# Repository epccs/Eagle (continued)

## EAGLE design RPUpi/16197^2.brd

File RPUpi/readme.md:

[RPUpi]

Shield to interface a Pi Zero hardware UART with a managed multidrop serial.

[RPUpi]: https://github.com/epccs/RPUpi/

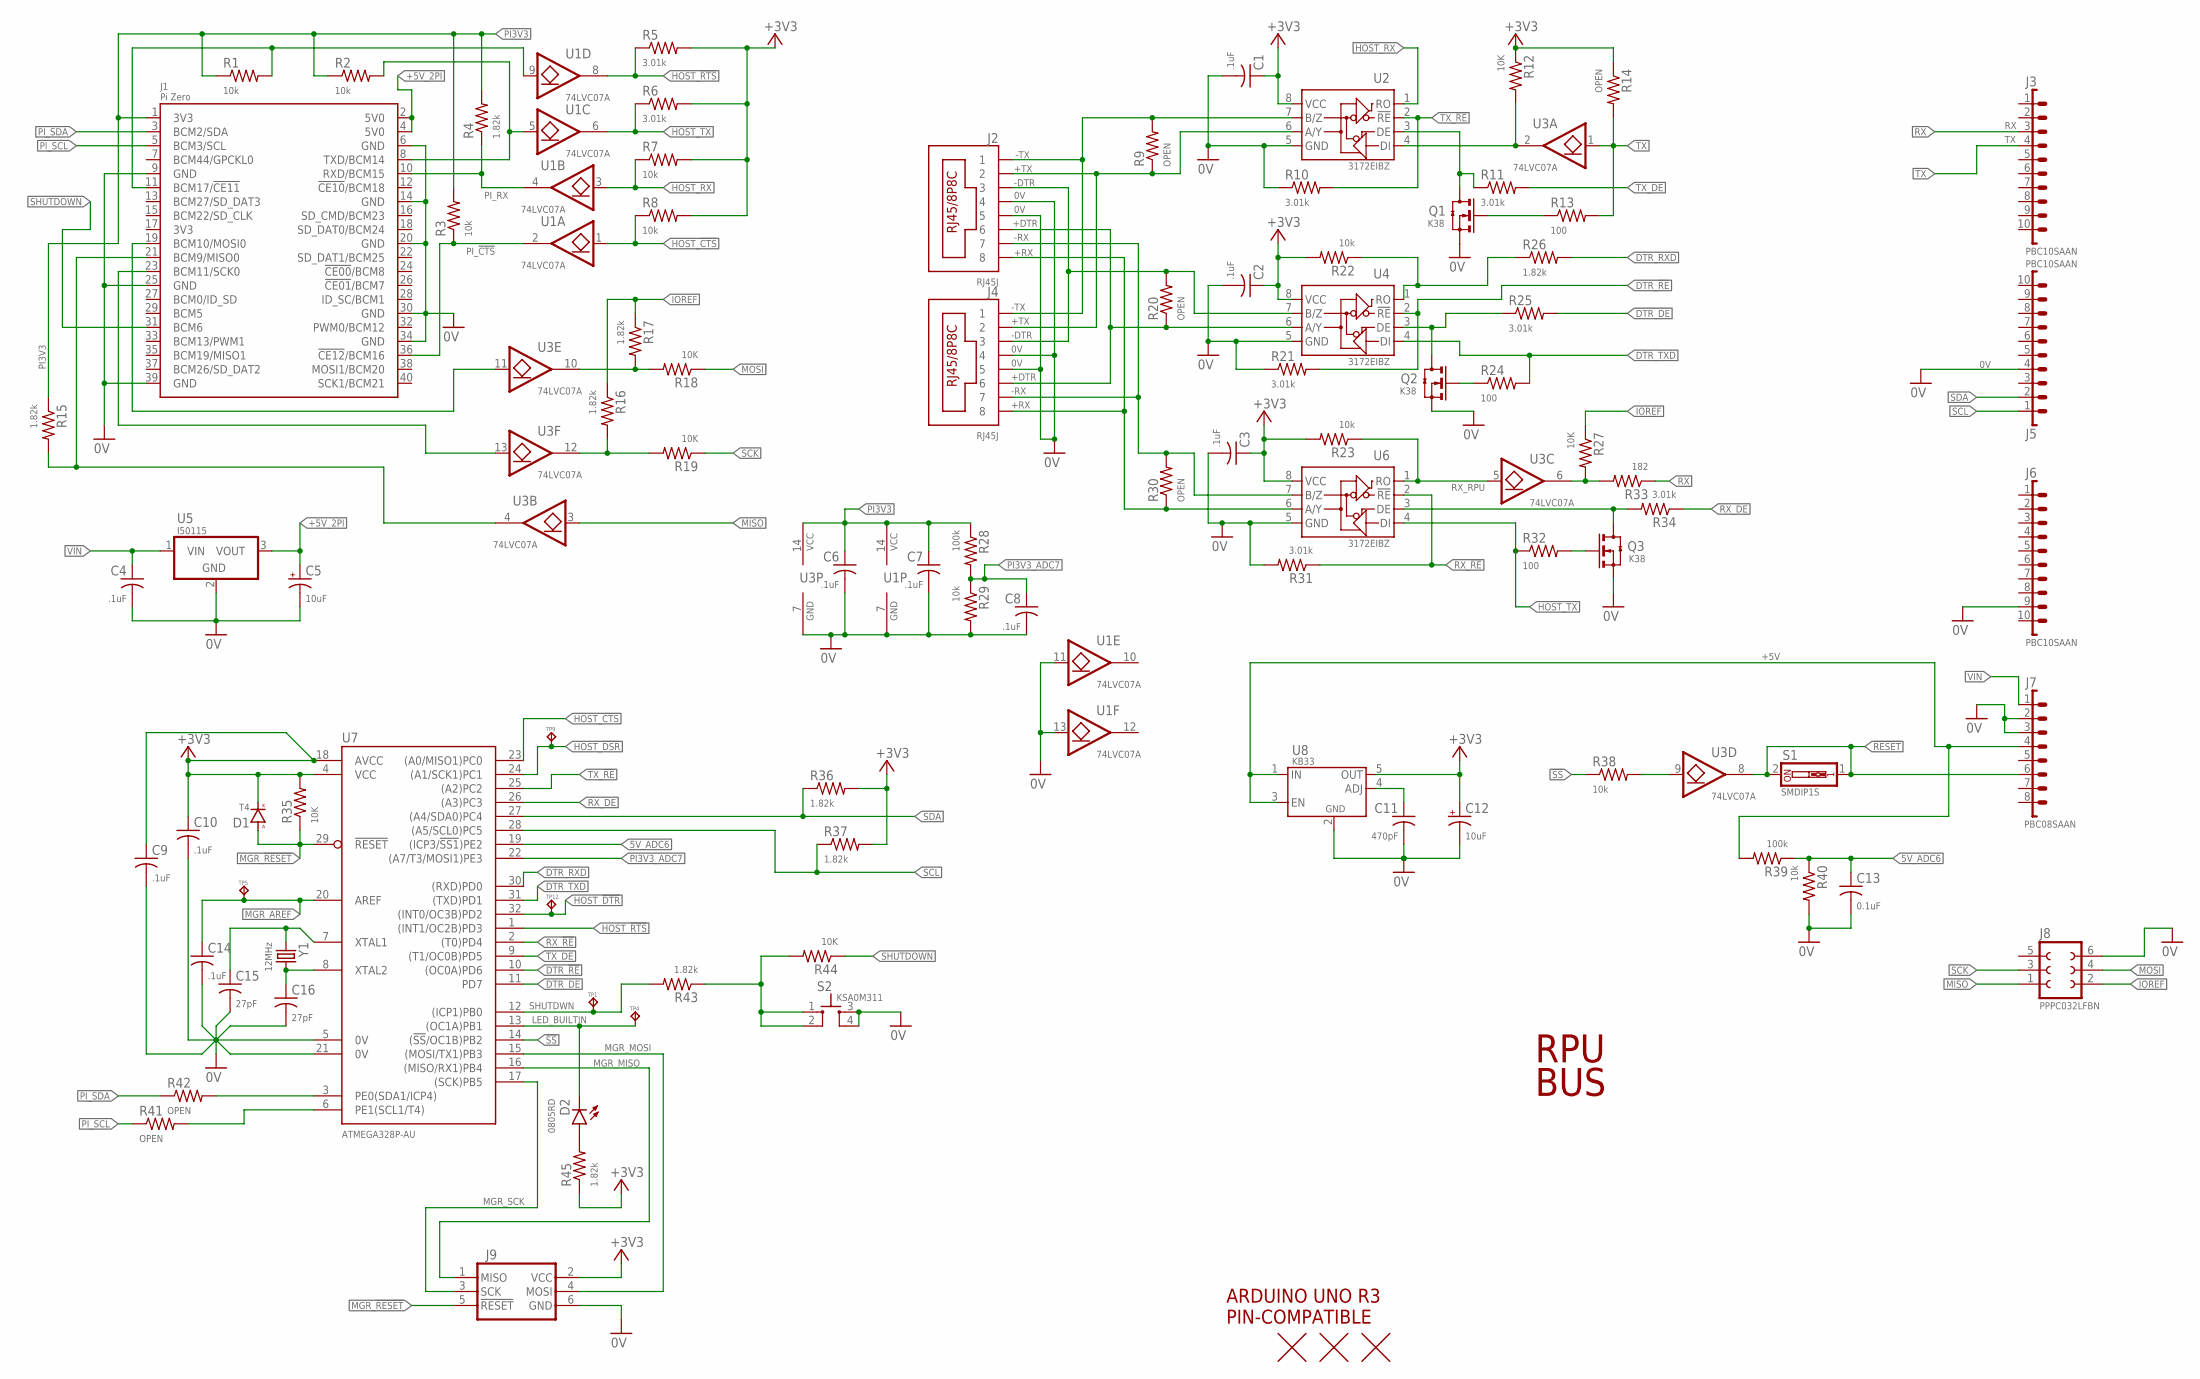
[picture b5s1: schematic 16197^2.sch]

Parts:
C1, C2, C3, C4, C6, C7, C8, C9, C10, C14: .1uF; C0603(1608)
C5, C12: 10uF; 3216
C11: 470pF; C0603(1608)
C13: 0.1uF; C0603(1608)
C15, C16: 27pF; C0603(1608)
D1: T4; SOD123
D2: 0805RD; C0805(2012)
J1: Pi Zero; RASPI_ZERO_V40PIN
J2, J4: RJ45J; RJ45-8HZT
J3, J5, J6: PBC10SAAN; 1X10
J7: PBC08SAAN; 1X8
J8: PPPC032LFBN; F2X3
J9: ISP-SPIPTH; ISP
Q1, Q2, Q3: K38; SOT23
R1, R2, R3, R7, R8, R22, R23, R29, R38, R40: 10k; C0805(2012)
R4, R15, R16, R17, R26, R36, R37, R43, R45: 1.82k; C0805(2012)
R5, R6, R10, R11, R21, R25, R31, R34: 3.01k; C0805(2012)
R9, R14, R20, R30, R41, R42: OPEN; C0805(2012)
R12, R18, R19, R27, R35, R44: 10K; C0805(2012)
R13, R24, R32: 100; C0805(2012)
R28, R39: 100k; C0805(2012)
R33: 182; C0805(2012)
S1: SMDIP1S; SMD-DIPSWITCH-1
S2: KSA0M311; 0M311
TP1, TP4, TP5, TP9, TP12: TPPAD1-08; P1-08
U1, U3: 74LVC07A; 14SOIC
U2, U4, U6: 3172EIBZ; SOIC8
U5: I50115; OKI-78SR-H
U7: ATMEGA328P-AU; TQFP32-08
U8: KB33; SOT23-5,SOT25
U$1: ARDUINO-UNO; ARDUINO_UNO
U$2, U$3, U$4: FIDUCIAL1.27; FIDUCIAL-1.27
Y1: 12MHz; CSM-3X

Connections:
0V: C1.2, C2.2, C3.2, C4.2, C5.-, C6.2, C7.2, C8.2, C9.2, C10.2, C11.2, C12.-, C13.2, C14.2, C15.2, C16.2, J1.6 (GND), J1.9 (GND), J1.14 (GND), J1.20 (GND), J1.25 (GND), J1.30 (GND), J1.34 (GND), J1.39 (GND), J2.4, J2.5, J4.4, J4.5, J5.4, J6.9, J7.2, J7.3, J8.6, J9.6 (GND), Q1.2(S) (S), Q2.2(S) (S), Q3.2(S) (S), R10.1, R21.1, R29.2, R31.2, R40.2, S2.3, S2.4, U1.7 (GND), U1.11 (I), U1.13 (I), U2.5 (GND), U3.7 (GND), U4.5 (GND), U5.2 (GND), U6.5 (GND), U7.5 (0V), U7.21 (0V), U8.2 (GND)
5V_ADC6: C13.1, R39.1, R40.1, U7.19 ((ICP3/!SS1!)PE2)
!RESET: J7.6, S1.1, S1.2, U3.8 (O)
!SS!: R38.1, U7.14 ((!SS!/OC1B)PB2)
+3V3: C1.1, C2.1, C3.1, C9.1, C10.1, C12.+, D1.C (K), J9.2 (VCC), R5.2, R6.2, R7.2, R8.2, R12.1, R14.1, R22.2, R23.2, R35.2, R36.2, R37.2, R45.1, U2.8 (VCC), U4.8 (VCC), U6.8 (VCC), U7.4 (VCC), U7.18 (AVCC), U8.5 (OUT)
+5V: J7.4, R39.2, U8.1 (IN), U8.3 (EN)
+5V_2PI: C5.+, J1.2 (5V0), J1.4 (5V0), U5.3 (VOUT)
+DTR: J2.6, J4.6, R20.1, U4.6 (A/Y)
+RX: J2.8, J4.8, R30.1, U6.6 (A/Y)
+TX: J2.2, J4.2, R9.1, U2.6 (A/Y)
-DTR: J2.3, J4.3, R20.2, U4.7 (B/Z)
-RX: J2.7, J4.7, R30.2, U6.7 (B/Z)
-TX: J2.1, J4.1, R9.2, U2.7 (B/Z)
DTR_!RE: R21.2, U4.2 (!RE), U7.10 ((OC0A)PD6)
DTR_DE: R25.2, U7.11 (PD7)
DTR_RXD: R26.2, U7.30 ((RXD)PD0)
DTR_TXD: R24.2, U4.4 (DI), U7.31 ((TXD)PD1)
HOST_!CTS: R8.1, U1.1 (I), U7.23 ((A0/MISO1)PC0)
HOST_!DSR: TP9.TP, U7.24 ((A1/SCK1)PC1)
HOST_!DTR: TP12.TP, U7.32 ((INT0/OC3B)PD2)
HOST_!RTS: R5.1, U1.8 (O), U7.1 ((INT1/OC2B)PD3)
HOST_MISO: J1.21 (BCM9/MISO0), R15.2, U3.4 (O)
HOST_MOSI: J1.19 (BCM10/MOSI0), U3.11 (I)
HOST_RX: R7.1, U1.3 (I), U2.1 (RO)
HOST_SCK: J1.23 (BCM11/SCK0), U3.13 (I)
HOST_TX: R6.1, R32.1, U1.6 (O), U6.4 (DI)
IOREF: J8.2, R16.1, R17.1, R27.1
LED_BUILTIN: D2.K, TP4.TP, U7.13 ((OC1A)PB1)
MGR_!RESET: D1.A, J9.5 (!RESET), R35.1, U7.29 (!RESET)
MGR_AREF: C14.1, TP5.TP, U7.20 (AREF)
MGR_MISO: J9.1 (MISO), U7.16 ((MISO/RX1)PB4)
MGR_MOSI: J9.4 (MOSI), U7.15 ((MOSI/TX1)PB3)
MGR_SCK: J9.3 (SCK), U7.17 ((SCK)PB5)
MISO: J8.1, U3.3 (I)
MOSI: J8.4, R18.1
unnamed: J1.8 (TXD/BCM14), R2.2, U1.5 (I)
unnamed: R38.2, U3.9 (I)
unnamed: J1.11 (BCM17/!CE11!), R1.2, U1.9 (I)
unnamed: R16.2, R19.2, U3.12 (O)
unnamed: R17.2, R18.2, U3.10 (O)
unnamed: R43.1, R44.2, S2.1, S2.2
unnamed: R27.2, R33.2, U3.6 (O)
unnamed: Q3.3(D) (D), R34.2, U6.3 (DE)
unnamed: Q1.1(G) (G), R13.1
unnamed: Q1.3(D) (D), R11.1, U2.3 (DE)
unnamed: R22.1, R26.1, U4.1 (RO)
unnamed: Q2.3(D) (D), R25.1, U4.3 (DE)
unnamed: Q2.1(G) (G), R24.1
unnamed: C11.1, U8.4 (ADJ)
unnamed: Q3.1(G) (G), R32.2
unnamed: D2.A, R45.2
PI3V3: C6.1, C7.1, J1.1 (3V3), R1.1, R2.1, R3.2, R4.2, R15.1, R28.1, U1.14 (VCC), U3.14 (VCC)
PI3V3_ADC7: C8.1, R28.2, R29.1, U7.22 ((A7/T3/MOSI1)PE3)
PI_!CTS: J1.36 (!CE12!/BCM16), R3.1, U1.2 (O)
PI_RX: J1.10 (RXD/BCM15), R4.1, U1.4 (O)
PI_SCL: J1.5 (BCM3/SCL), R41.1
PI_SDA: J1.3 (BCM2/SDA), R42.1
RX: J3.3, R33.1
RX_!RE: R31.1, U6.2 (!RE), U7.2 ((T0)PD4)
RX_DE: R34.1, U7.26 ((A3)PC3)
RX_RPU: R23.1, U3.5 (I), U6.1 (RO)
SCK: J8.3, R19.1
SCL: J5.1, R37.1, U7.28 ((A5/SCL0)PC5)
SCL1: R41.2, U7.6 (PE1(SCL1/T4))
SDA: J5.2, R36.1, U7.27 ((A4/SDA0)PC4)
SDA1: R42.2, U7.3 (PE0(SDA1/ICP4))
SHUTDOWN: J1.31 (BCM6), R44.1
SHUTDWN: R43.2, TP1.TP, U7.12 ((ICP1)PB0)
TX: J3.4, R13.2, R14.2, U3.1 (I)
TX_!RE: R10.2, U2.2 (!RE), U7.25 ((A2)PC2)
TX_DE: R11.2, U7.9 ((T1/OC0B)PD5)
TX_RPU: R12.2, U2.4 (DI), U3.2 (O)
VIN: C4.1, J7.1, U5.1 (VIN)
XTAL1: C15.1, U7.7 (XTAL1), Y1.1
XTAL2: C16.1, U7.8 (XTAL2), Y1.2

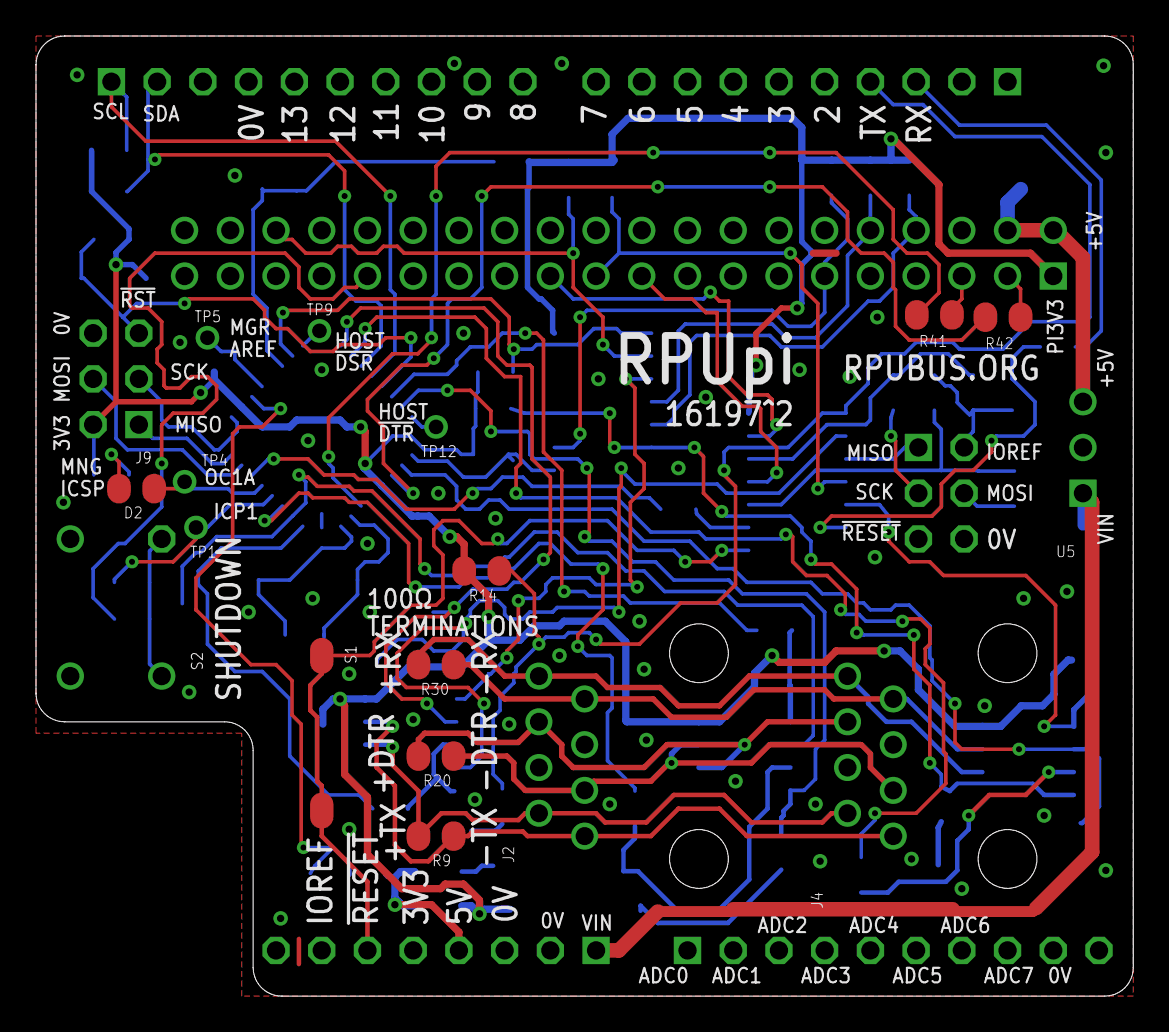
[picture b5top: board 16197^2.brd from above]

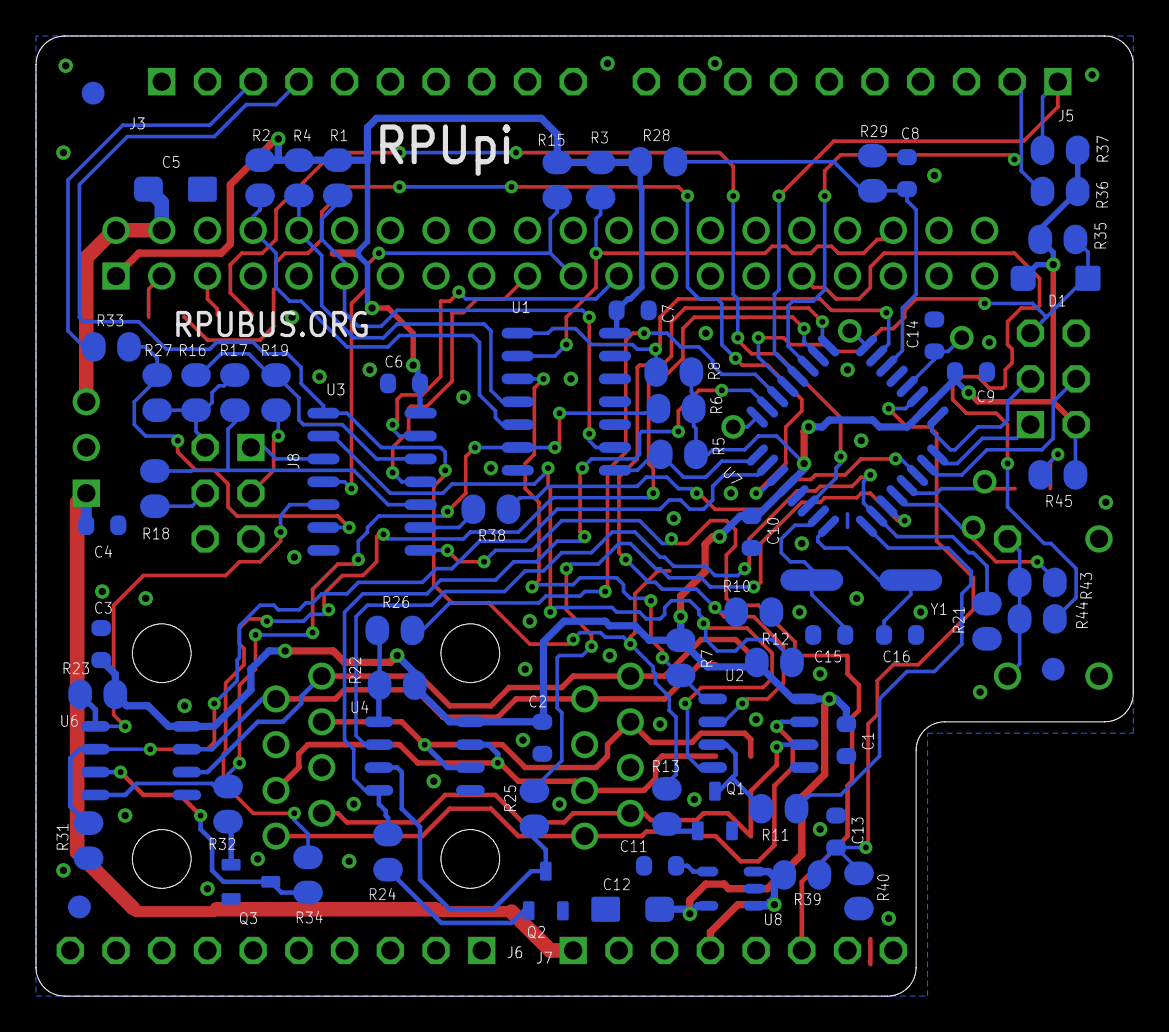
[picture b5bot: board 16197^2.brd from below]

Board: 2 copper layers, 61.0 x 53.3 mm, 95 parts (75 on the bottom side), 75 nets.
